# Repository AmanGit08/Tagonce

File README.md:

SAMT — Air Tag Project

Compact, low-power tracking device built with an ESP32-PICO, u-blox NEO-M8 GPS, USB-C charging (MCP73871), and a 3.3V buck regulator. This repository holds the KiCad schematics, PCB, BOM and build notes for a compact, production-ready AirTag-style tracker.

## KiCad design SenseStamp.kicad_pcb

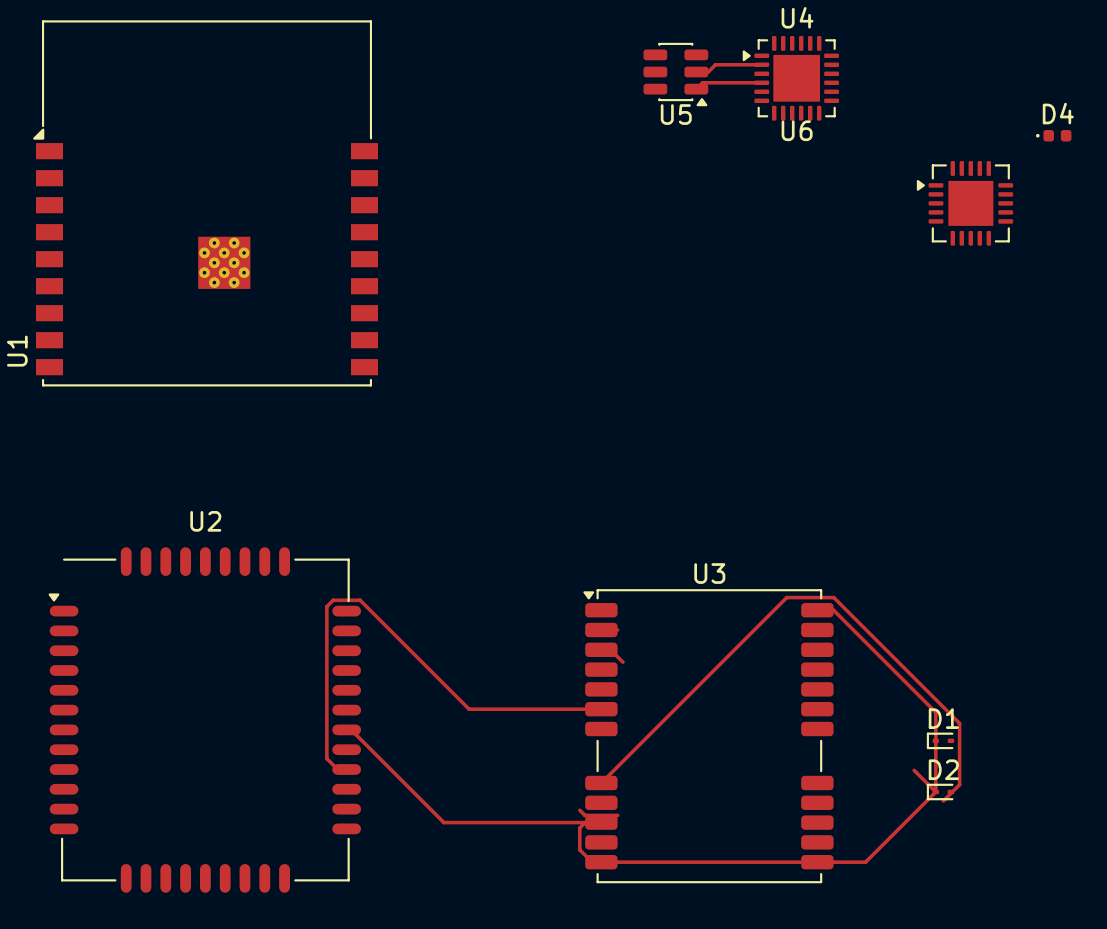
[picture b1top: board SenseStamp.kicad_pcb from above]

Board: 2 copper layers, 9 parts (0 on the bottom side), 19 nets.

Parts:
D1, D2: ESD9B3.3ST5G; D_SOD-923
D4: LTST-C235KGKRKT; LED_0402_1005Metric
U1: ESP32-C3-WROOM-02
U2: SIM7020E; SIMCom_SIM800C
U3: NEO-M8M; ublox_NEO
U4: CP2102N-Axx-xQFN24; QFN-24-1EP_4x4mm_P0.5mm_EP2.6x2.6mm
U5: USBLC6-2SC6; SOT-23-6
U6: MCP73871; QFN-20-1EP_4x4mm_P0.5mm_EP2.5x2.5mm

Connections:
+3.3V: D4.2 (A2), U4.6 (VDD), U4.7 (VREGIN)
/BOOT: U1.8 (IO9), U3.1 (~SAFEBOOT)
/GPIO 18: U1.13 (IO18), U2.29 (GPIO1)
/GPIO 19: U1.14 (IO19), U2.10 (GPIO0)
/MISO_DO: U1.16 (IO2), U3.21 (RXD/SPI_MOSI)
/RX_TX: U1.12 (IO21/TXD), U2.2 (UART1_RXD)
/SCL: U1.15 (IO3), U3.19 (SCL/SPI_CLK)
/SDA: U1.3 (IO4), U3.18 (SDA/~SPI_CS)
/TX_RX: U1.11 (IO20/RXD), U2.1 (UART1_TXD)
/USB CHARGER/USB_D+: U4.3 (D+), U5.3 (I/O2)
/USB CHARGER/USB_D-: U4.4 (D-), U5.1 (I/O1)
/USB_DP: U2.25 (USB_DP), U3.6 (USB_DP)
/VBAT: U2.34 (VBAT), U2.35 (VBAT)
GND: D1.1 (A1), D2.1 (A1), U1.9 (GND), U1.19 (GND), U2.8 (GND), U2.13 (GND), U2.19 (GND), U2.21 (GND), U2.27 (GND), U2.30 (GND), U2.31 (GND), U2.33 (GND), U2.36 (GND), U2.37 (GND), U3.2 (D_SEL), U3.10 (GND), U3.12 (GND), U3.13 (GND), U3.24 (GND), U4.2 (GND), U4.25 (GND), U5.2 (GND)
unnamed: U6.18 (IN), U6.19 (IN)
unnamed: U6.1 (OUT), U6.20 (OUT)
unnamed: U6.14 (V_{BAT}), U6.15 (V_{BAT})
unnamed: U6.10 (V_{SS}), U6.11 (V_{SS}), U6.21 (V_{SS})
RESET: D2.2 (A2), U3.8 (~RESET)

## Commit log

2025-10-16 Enhance README with device description
    Added a brief description of the Tagonce device.
2025-10-20 Revise README for SAMT Air Tag Project
    Updated project name and description for clarity.
2025-10-28 Add MIT License to the project
2026-02-20 this is the new schamatic file update
2026-02-21 pressure sensor sch and bak file
2026-02-21 ESP32 FILE
2026-02-21 fp-info-cache updated
2026-02-22 SenseStamp.kicad_pcb updated
